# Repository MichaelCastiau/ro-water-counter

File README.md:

# RO Water Counter

This repository contains the source code and hardware schematics for a Reverse Osmosis water counter device, based on an ESP32 module. The device allows for setting an amount of needed liters of water an will swich on/off the RO system automatically. When the amount of liters needed has been reached, the ESP32 module is programmed to interact with a webhook to send a notification to your smartphone.

It interfaces with a high-precision water flow sensor with a K-factor of 20.

## Flashing

```shell
python -m esptool  --port /dev/tty.usbserial-1420 --chip esp32 write_flash 0x00010000 .pio/build/esp32/firmware.bin
```
### Bootloader

The ESP32 requires a second stage bootloader that will read the partition table and boot the corresponding app.
The booloader is located in the `bootloader.bin` file and should be flashed at address 0x1000 in the flash.

```shell
python -m esptool  --port /dev/tty.usbmodem14301 --chip esp32 write_flash 0x1000 bootloader.bin
```

### Partition Table

This project utilises a custom partition table to make enough room for OTA updates.
The partition definitions can be found in `partitions.csv` file. The partition table should be flashed
at address 0x8000 in  the flash after building the project with PlatformIO.

```shell
python -m esptool  --port /dev/tty.usbmodem14301 --chip esp32 write_flash 0x8000 .pio/build/default/partitions.bin
```

### Application

The application itself should be flashed at address 0x10000 (or 0x210000 if using OTA), corresponding to the address defined in the bootloader table.

```shell
python -m esptool  --port /dev/tty.usbmodem14301 --chip esp32 write_flash 0x10000 .pio/build/default/firmware.bin
```

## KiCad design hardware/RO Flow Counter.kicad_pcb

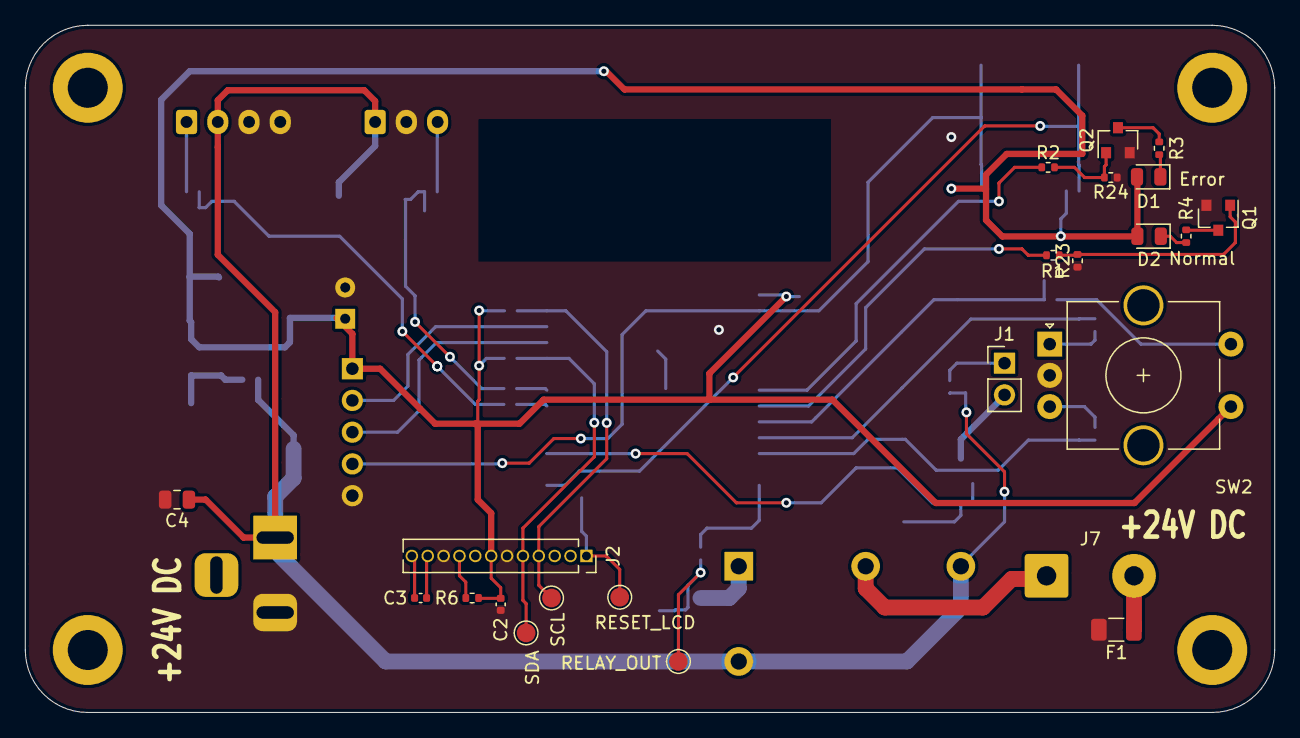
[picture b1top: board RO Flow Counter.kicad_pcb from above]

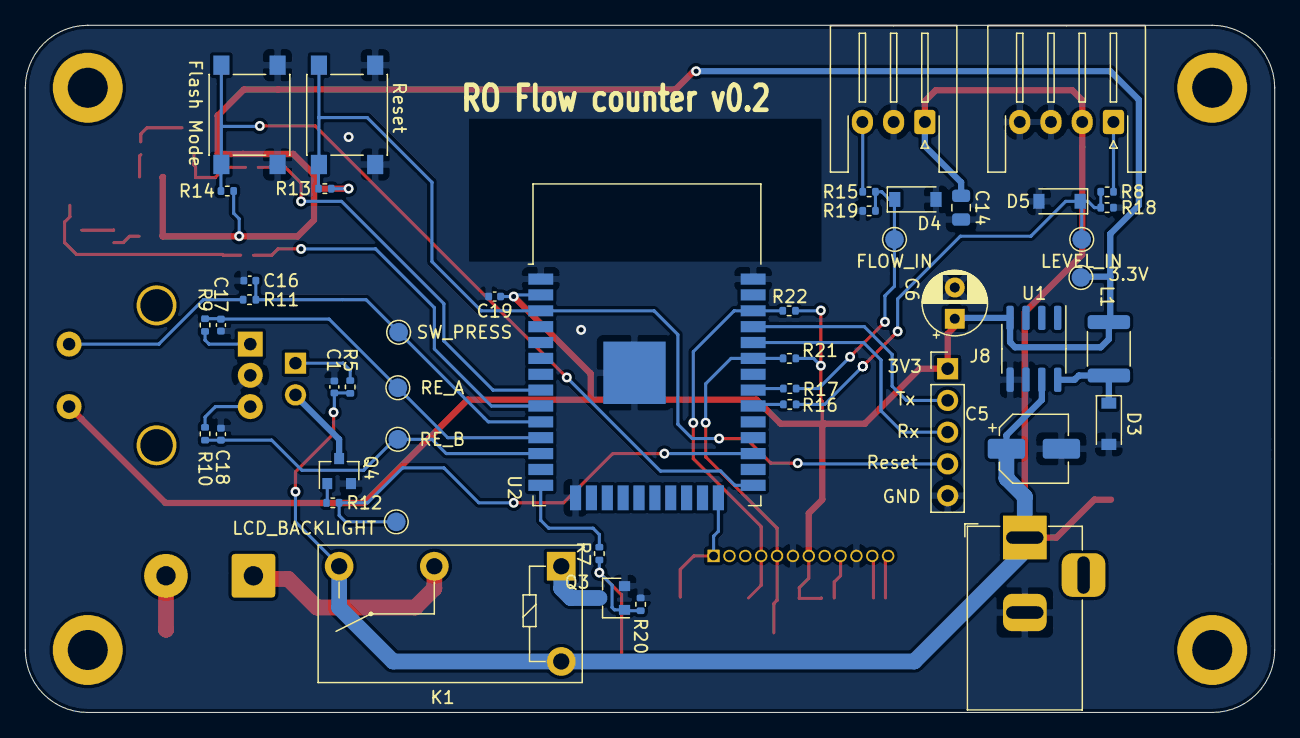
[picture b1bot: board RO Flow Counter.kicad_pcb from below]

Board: 2 copper layers, 100.0 x 55.0 mm, 74 parts (47 on the bottom side), 43 nets.

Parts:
C1, C2, C3, C16: 100nF; C_0402_1005Metric
C4: 22uF; C_0805_2012Metric
C5: 68uF; CP_Elec_5x5.4
C6: 120uF; CP_Radial_D5.0mm_P2.50mm
C14: 4.7uF; C_0805_2012Metric
C17, C18, C19: 0.1uF; C_0402_1005Metric
D1: Error; LED_0805_2012Metric
D2: Normal Operation; LED_0805_2012Metric
D3: 1N5817; D_SOD-123
D4, D5: 3V3; D_SOD-123
F1: 10A; Fuse_1206_3216Metric
H1, H2, H3, H4: MountingHole; MountingHole_3.2mm_M3_DIN965_Pad
J1: LCD Power; PinHeader_1x02_P2.54mm_Vertical
J2: Conn_01x12; PinSocket_1x12_P1.27mm_Vertical
J3: Barrel_Jack; BarrelJack_Horizontal
J5: Flow Meter; JST_XH_S3B-XH-A-1_1x03_P2.50mm_Horizontal
J6: Level Sensor (optional); JST_XH_S4B-XH-A-1_1x04_P2.50mm_Horizontal
J7: Conn_01x02; SolderWire-0.75sqmm_1x02_P7mm_D1.25mm_OD3.5mm
J8: Programming; PinHeader_1x05_P2.54mm_Vertical
K1: G5Q-1A; Relay_SPST_Omron-G5Q-1A
L1: 100uH; L_1812_4532Metric
Q1, Q2, Q3, Q4: 2N7002E; SOT-23
R1, R2, R7, R9, R10, R11, R12, R16, R17: 1k; R_0402_1005Metric
R3: 154; R_0402_1005Metric
R4: 140; R_0402_1005Metric
R5: 1k4; R_0402_1005Metric
R6, R8, R13, R14, R19, R20, R23, R24: 10k; R_0402_1005Metric
R15, R21, R22: 5k6; R_0402_1005Metric
R18: 1k56; R_0402_1005Metric
SW2: Rotary_Encoder_Switch; RotaryEncoder_Alps_EC11E-Switch_Vertical_H20mm_CircularMoun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
SW3: Reset; SW_Push_1P1T_NO_6x6mm_H9.5mm
SW4: Flash Mode; SW_Push_1P1T_NO_6x6mm_H9.5mm
TP1: 3.3V; TestPoint_Pad_D1.5mm
TP2: SW_PRESS; TestPoint_Pad_D1.5mm
TP3: RE_A; TestPoint_Pad_D1.5mm
TP4: RELAY_OUT; TestPoint_Pad_D1.5mm
TP5: RE_B; TestPoint_Pad_D1.5mm
TP6: SDA; TestPoint_Pad_D1.5mm
TP7: LEVEL_IN; TestPoint_Pad_D1.5mm
TP8: RESET_LCD; TestPoint_Pad_D1.5mm
TP9: FLOW_IN; TestPoint_Pad_D1.5mm
TP11: SCL; TestPoint_Pad_D1.5mm
TP12: LCD_BACKLIGHT; TestPoint_Pad_D1.5mm
U1: LM2594HVM-3.3; SOIC-8_3.9x4.9mm_P1.27mm
U2: ESP32-WROOM-32

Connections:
+3V3: C2.1, C6.1, C19.1, D1.2, D2.2, J2.7, J8.1, L1.2, R6.2, R13.1, R14.1, R21.1, R22.1, SW2.S1, TP1.1, U1.4, U2.2
+24V: C1.2, C4.1, C5.1, C14.1, J3.1, J5.1, J6.2, K1.3, K1.5, R5.2, U1.7
/display/BACKLIGHT_LCD: R12.2, TP12.1, U2.27
/display/RESET_DISPLAY: J2.1, TP8.1, U2.24
/display/SCL: J2.4, R22.2, TP11.1, U2.36
/display/SDA: J2.5, R21.2, TP6.1, U2.33
/mcu/ERROR_OUT: R2.1, U2.8
/mcu/FLOW_IN: R17.1, U2.31
/mcu/LEVEL_IN: R16.1, U2.30
/mcu/NORMAL_OPERATION_OUT: R1.1, U2.9
/mcu/RELAY_OUT: R7.2, U2.14
/mcu/RE_A: C17.1, R9.2, TP3.1, U2.11
/mcu/RE_B: C18.1, R10.2, TP5.1, U2.12
/mcu/RX: J8.3, U2.34
/mcu/SW_PRESS: C16.1, R11.1, TP2.1, U2.10
/mcu/TX: J8.2, U2.35
/mcu/reset: J8.4, R13.2, SW3.2, U2.3
GND: C1.1, C2.2, C4.2, C5.2, C6.2, C14.2, C16.2, C17.2, C18.2, C19.2, D3.2, D4.2, D5.2, F1.2, J2.6, J2.10, J3.2, J5.2, J6.3, J6.4, J8.5, Q1.2, Q2.2, Q3.2, Q4.2, R18.2, R19.2, R20.1, R23.1, R24.1, SW2.C, SW3.1, SW4.2, U1.5, U1.6, U2.1, U2.15, U2.38, U2.39
unnamed: C3.1, J2.12
unnamed: C3.2, J2.11
unnamed: D1.1, R3.1
unnamed: D2.1, R4.1
unnamed: D3.1, L1.1, U1.8
unnamed: D4.1, R15.2, R17.2, R19.1, TP9.1
unnamed: D5.1, R8.2, R16.2, R18.1, TP7.1
unnamed: F1.1, J7.2
unnamed: J1.1, R5.1
unnamed: J1.2, Q4.3
unnamed: J2.9, R6.1
unnamed: J5.3, R15.1
unnamed: J6.1, R8.1
unnamed: J7.1, K1.2
unnamed: K1.1, Q3.3
unnamed: Q1.1, R1.2, R23.2
unnamed: Q1.3, R4.2
unnamed: Q2.1, R2.2, R24.2
unnamed: Q2.3, R3.2
unnamed: Q3.1, R7.1, R20.2, TP4.1
unnamed: Q4.1, R12.1
unnamed: R9.1, SW2.A
unnamed: R10.1, SW2.B
unnamed: R11.2, SW2.S2
unnamed: R14.2, SW4.1, U2.25

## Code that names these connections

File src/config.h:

#define PIN_RESET_LCD                   2
#define PIN_RELAY_OUT                   12
#define PIN_LCD_BACKLIGHT               16
#define PIN_LEVEL_IN                    18
#define PIN_FLOW_IN                     19
#define RE_PRESS                        25  // rotary encoder press
#define RE_A                            26  // rotary encoder A
#define RE_B                            27  // rotary encoder B
#define LED_ERROR                       32
#define LED_NORMAL                      33
#define LED_WIFI                        13

// Modes
#define MODE_MENU                       (uint8_t)(1 << 1)
#define MODE_RUNNING                    (uint8_t)(1 << 2)
#define MODE_PAUZED                     (uint8_t)(1 << 3)

// Rotary encoder
#define RE_STEPS                        (double) 0.5
#define RE_ROTATE_CLOCKWISE             (1 << 1)
#define RE_ROTATE_COUNTERCLOCKWISE      (1 << 0)

// FLow meter
#define FLOW_PERIOD_MS                   1000
#define RESET_FLOW_METER                 (1 << 0)
#define FLOW_METER_K_FACTOR              (double) 20.0

// LEDs events
#define LED_STATE_NORMAL_RUNNIN          (1 << 0)
#define LED_STATE_NORMAL_PAUZED          (1 << 1)
#define LED_STATE_ERROR                  (1 << 2)
#define LED_STATE_IDLE                   (1 << 3)
#define EN_BACKLIGHT                     (1 << 4)   // Every time event is fired, backlight is enabled for 30s

//LCD
#define BACKLIGHT_MAX                    203
#define BACKLIGHT_IDLE_MS                30000

// WiFi
#define WEBHOOKS_KEY                     (const char*)"bT83HL9K3aVx_YwVMMCmDC"
#define WIFI_CONNECTED                   (1 << 0)

// Water level
#define WATER_TOPPED_OFF                 (1 << 0)

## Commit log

2022-08-15 First successful lcd write
2022-08-15 integrate rotary encoder
2022-08-16 use mode accross entire device
2022-08-16 implement rotary encoder
2022-08-21 fix Q factor, use LEDs
2022-08-21 try to calibrate with flowcount library
2022-08-21 try to calibrate sensor
2022-08-22 Finish first implementation
2022-08-23 Use webhooks integration
2022-08-23 add hardware
2022-08-23 add fabrication outputs
2022-08-23 add hardware submodule
2022-08-23 add hardware as submodule
2022-08-25 fix: fix counter values not resetting
2022-08-25 add ato
2022-08-31 fix k factor
2022-09-03 k factor
2022-09-03 make it simpler
2022-09-04 version 2
2022-09-04 dim the backlight automatically
2022-12-02 change k factor
2022-12-09 feat: add webinterface with wesockets
2022-12-09 remove flow meter
2022-12-09 add websocket portal
2022-12-10 get time from the internet
2022-12-10 add space on portal
2022-12-10 fix estimate
2022-12-12 fix setting other liters target on pauze websocket
